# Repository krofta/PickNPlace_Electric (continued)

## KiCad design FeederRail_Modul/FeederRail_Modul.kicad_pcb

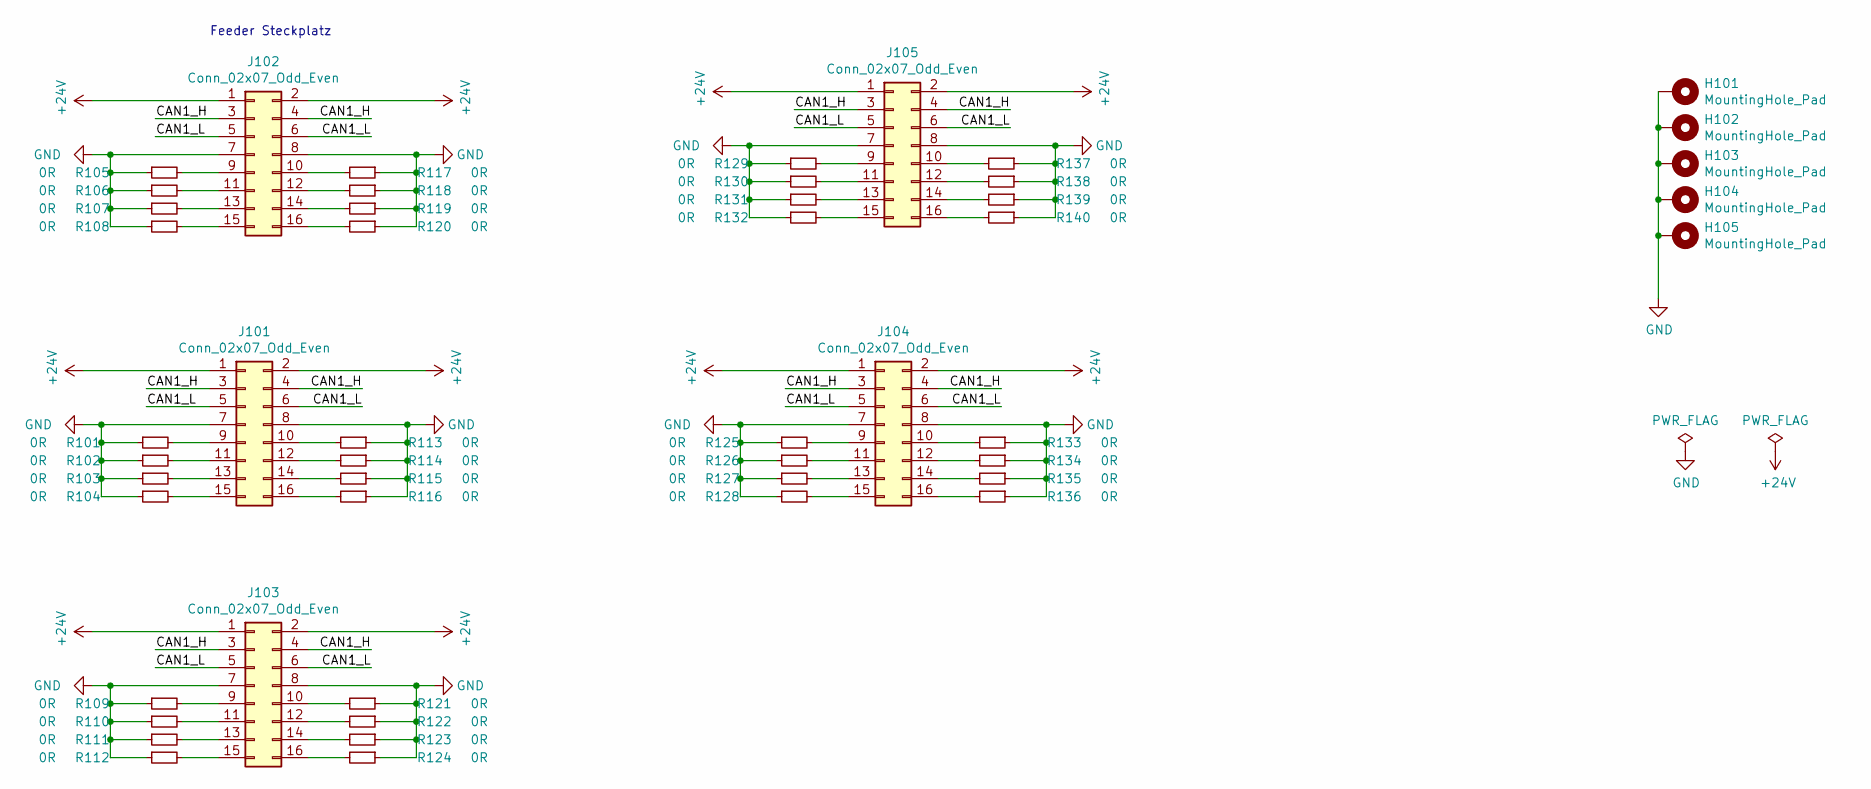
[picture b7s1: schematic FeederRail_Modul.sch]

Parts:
H101, H102, H103, H104, H105: MountingHole_Pad; MountingHole_4mm_Pad_Via; LCSC 0
J101, J102, J103, J104, J105: Conn_02x07_Odd_Even; PinHeader_2x08_P2.54mm_Vertical; LCSC C30734
R101, R102, R103, R104, R105, R106, R107, R108, R109, R110, R111, R112, R113, R114, R115, R116, R117, R118, R119, R120, R121, R122, R123, R124, R125, R126, R127, R128, R129, R130, R131, R132, R133, R134, R135, R136, R137, R138, R139, R140: 0R; R_0603_1608Metric; LCSC C384298

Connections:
+24V: J101.1, J101.2, J102.1, J102.2, J103.1, J103.2, J104.1, J104.2, J105.1, J105.2
/CAN1_H: J101.3, J101.4, J102.3, J102.4, J103.3, J103.4, J104.3, J104.4, J105.3, J105.4
/CAN1_L: J101.5, J101.6, J102.5, J102.6, J103.5, J103.6, J104.5, J104.6, J105.5, J105.6
GND: H101.1, H102.1, H103.1, H104.1, H105.1, J101.7, J101.8, J102.7, J102.8, J103.7, J103.8, J104.7, J104.8, J105.7, J105.8, R101.1, R102.1, R103.1, R104.1, R105.1, R106.1, R107.1, R108.1, R109.1, R110.1, R111.1, R112.1, R113.1, R114.1, R115.1, R116.1, R117.1, R118.1, R119.1, R120.1, R121.1, R122.1, R123.1, R124.1, R125.1, R126.1, R127.1, R128.1, R129.1, R130.1, R131.1, R132.1, R133.1, R134.1, R135.1, R136.1, R137.1, R138.1, R139.1, R140.1
unnamed: J101.9, R101.2
unnamed: J101.10, R113.2
unnamed: J101.11, R102.2
unnamed: J101.12, R114.2
unnamed: J101.13, R103.2
unnamed: J101.14, R115.2
unnamed: J101.15, R104.2
unnamed: J101.16, R116.2
unnamed: J102.9, R105.2
unnamed: J102.10, R117.2
unnamed: J102.11, R106.2
unnamed: J102.12, R118.2
unnamed: J102.13, R107.2
unnamed: J102.14, R119.2
unnamed: J102.15, R108.2
unnamed: J102.16, R120.2
unnamed: J103.9, R109.2
unnamed: J103.10, R121.2
unnamed: J103.11, R110.2
unnamed: J103.12, R122.2
unnamed: J103.13, R111.2
unnamed: J103.14, R123.2
unnamed: J103.15, R112.2
unnamed: J103.16, R124.2
unnamed: J104.9, R125.2
unnamed: J104.10, R133.2
unnamed: J104.11, R126.2
unnamed: J104.12, R134.2
unnamed: J104.13, R127.2
unnamed: J104.14, R135.2
unnamed: J104.15, R128.2
unnamed: J104.16, R136.2
unnamed: J105.9, R129.2
unnamed: J105.10, R137.2
unnamed: J105.11, R130.2
unnamed: J105.12, R138.2
unnamed: J105.13, R131.2
unnamed: J105.14, R139.2
unnamed: J105.15, R132.2
unnamed: J105.16, R140.2

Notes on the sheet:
Feeder Steckplatz

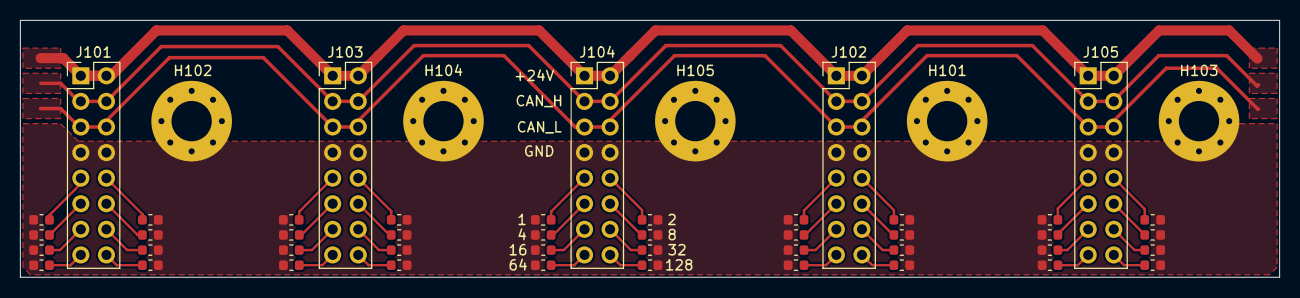
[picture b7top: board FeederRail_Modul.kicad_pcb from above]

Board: 2 copper layers, 125.0 x 25.5 mm, 50 parts (0 on the bottom side), 44 nets.

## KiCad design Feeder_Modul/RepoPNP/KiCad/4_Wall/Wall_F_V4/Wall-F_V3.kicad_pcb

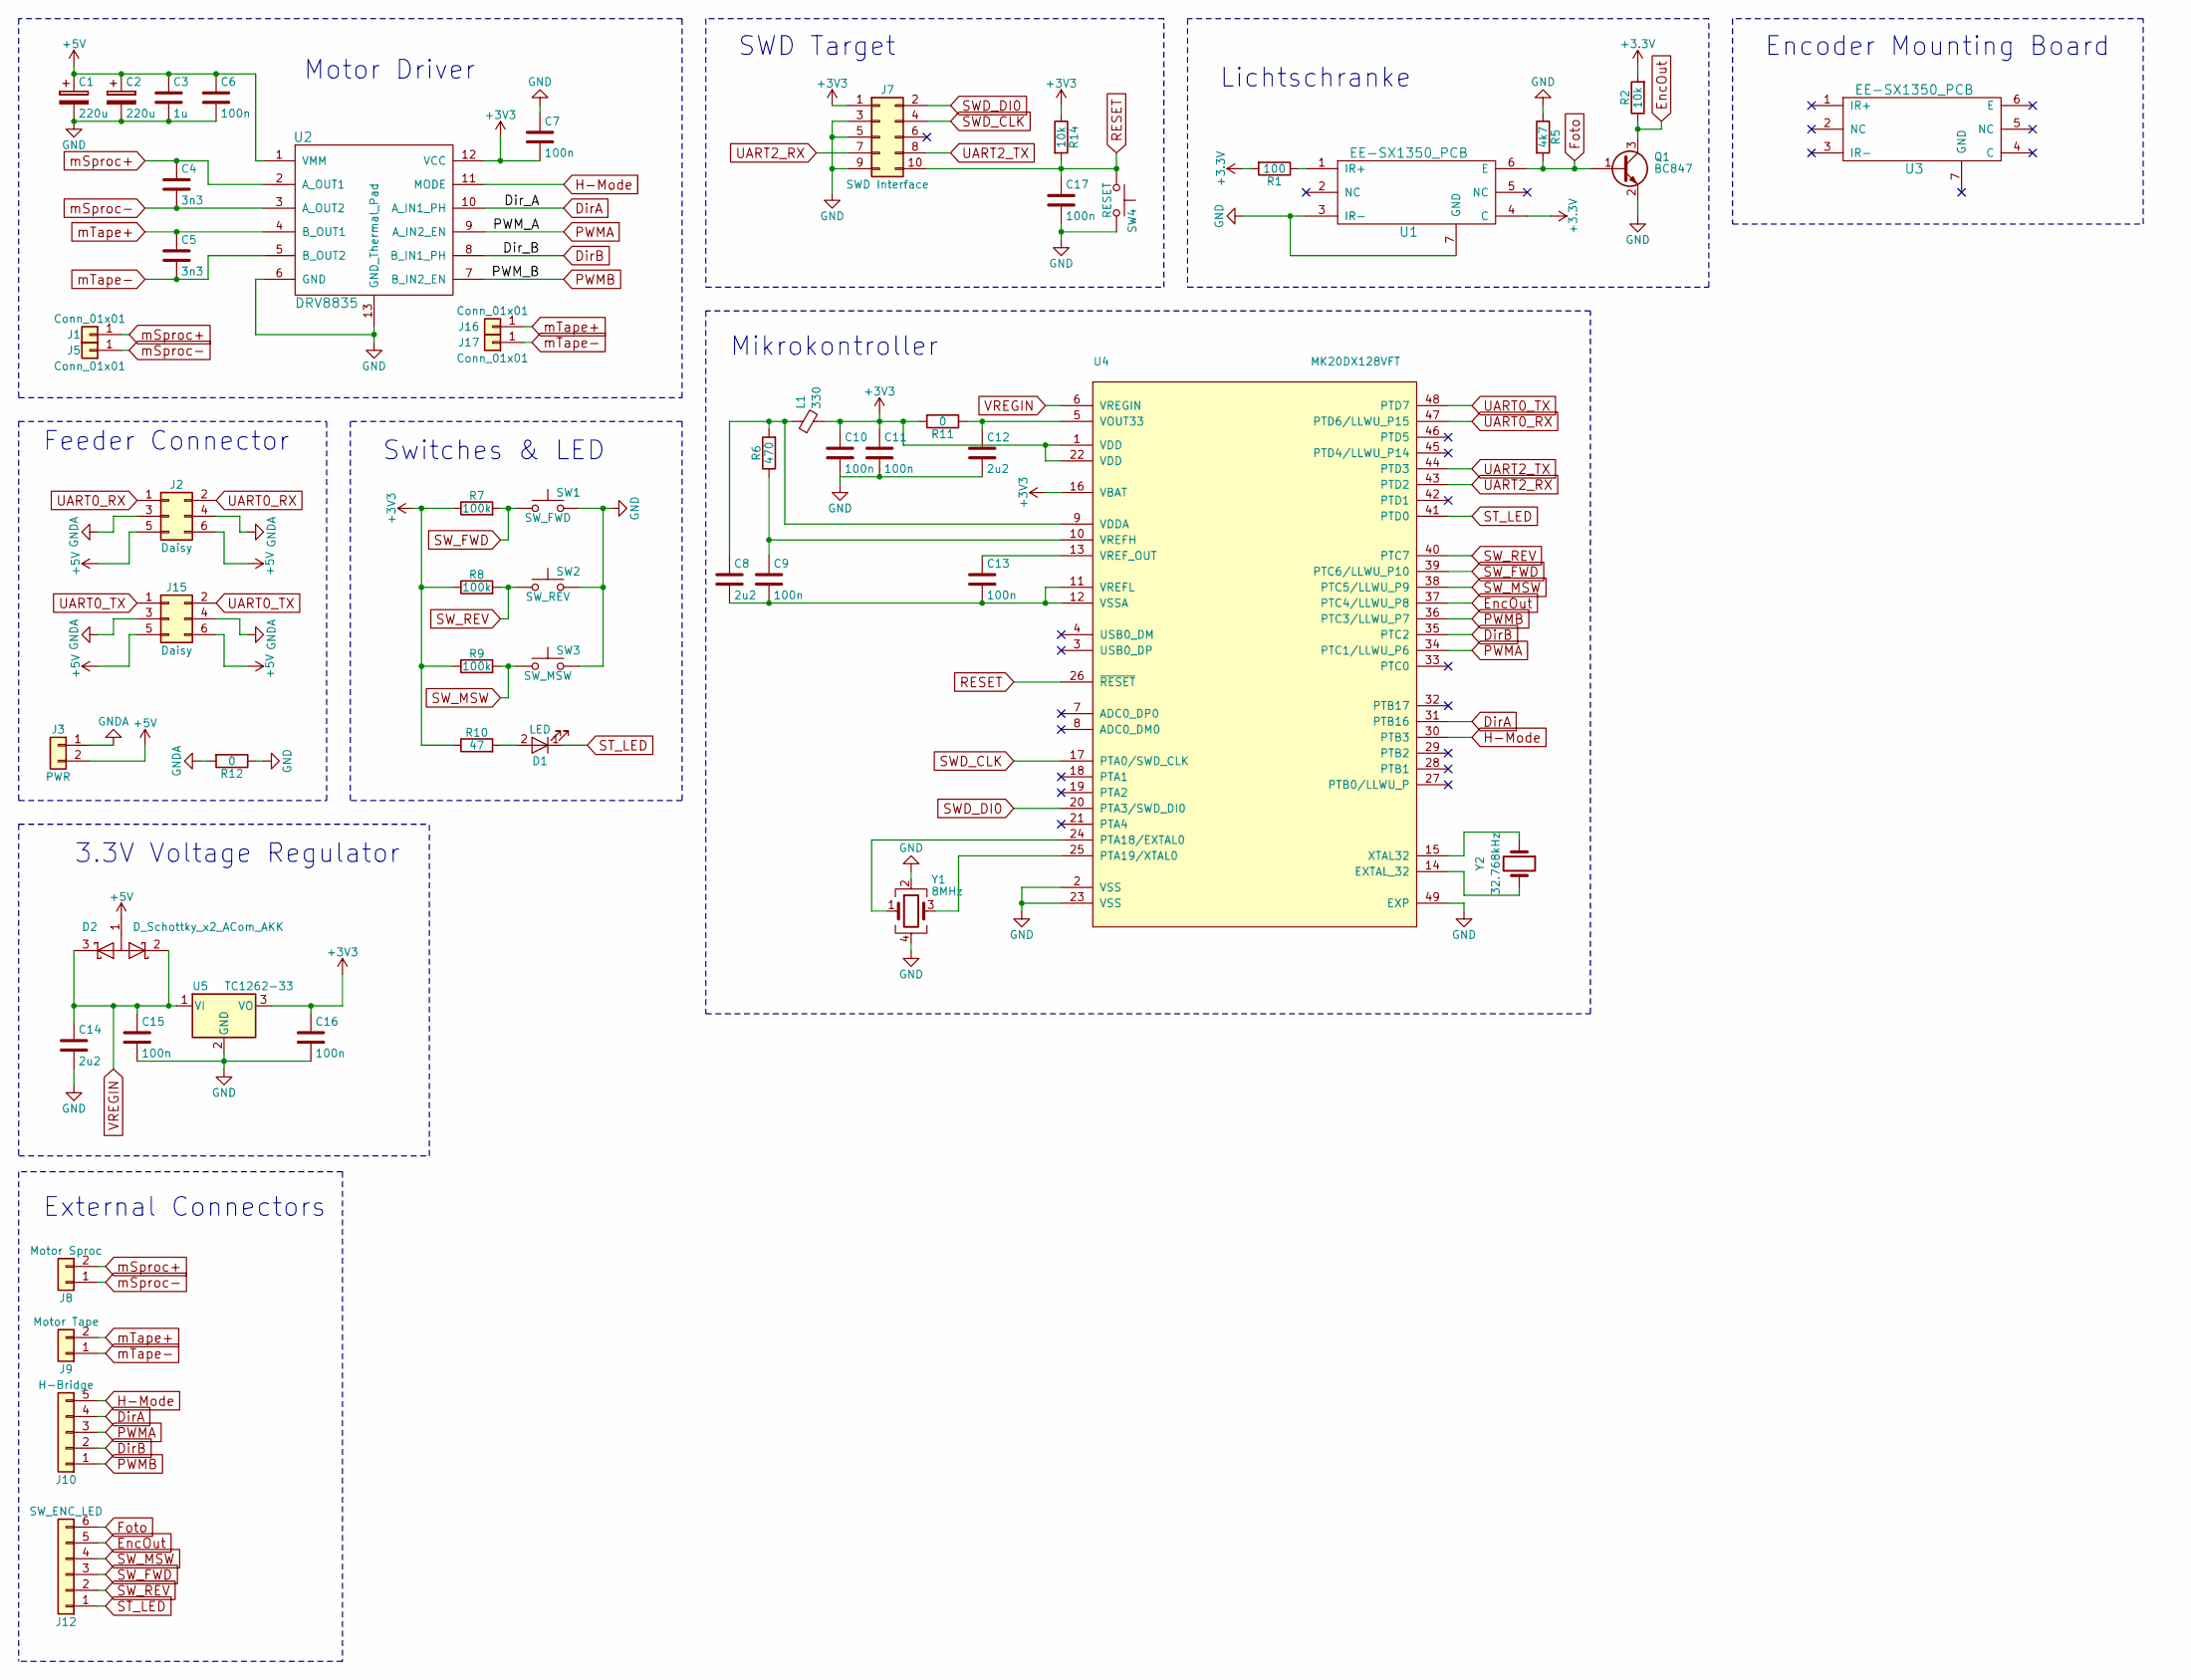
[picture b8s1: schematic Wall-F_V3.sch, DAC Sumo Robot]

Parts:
C1, C2: 220u; CP_Elec_6.3x7.7
C3: 1u; C_0805
C4, C5: 3n3; C_0805
C6, C7, C9, C10, C11, C13, C15, C16, C17: 100n; C_0805
C8, C12, C14: 2u2; C_0805
D1: LED; LED_0805
D2: D_Schottky_x2_ACom_AKK; SOT-23
J1, J5, J16, J17: Conn_01x01; Pin_Header_Straight_1x01_Pitch2.54mm
J2, J15: Daisy; Pin_Header_Angled_2x03_Pitch2.54mm
J3: PWR; Pin_Header_Straight_1x02_Pitch2.54mm
J7: SWD Interface; Pin_Header_Straight_2x05_Pitch1.27mm_SMD
J8: Motor Sproc; Pin_Header_Straight_1x02_Pitch2.54mm
J9: Motor Tape; Pin_Header_Straight_1x02_Pitch2.54mm
J10: H-Bridge; Pin_Header_Straight_1x05_Pitch2.54mm
J12: SW_ENC_LED; Pin_Header_Straight_1x06_Pitch2.54mm
L1: 330; L_0805
Q1: BC847; SOT-23
R1: 100; R_0805
R2, R14: 10k; R_0805
R5: 4k7; R_0805
R6: 470; R_0805
R7, R8, R9: 100k; R_0805
R10: 47; R_0805
R11, R12: 0; R_0805
SW1: SW_FWD; SW_SPST_B3S-1000_LONG
SW2: SW_REV; SW_SPST_B3S-1000_LONG
SW3: SW_MSW; Pin_Header_Straight_1x02_Pitch2.54mm
SW4: RESET; SW_SPST_B3S-1000_LONG
U1: EE-SX1350_PCB; EESX1350_PCB_V4
U2: DRV8835; WSON-12-1EP_3x2mm_Pitch0.5mm
U3: EE-SX1350_PCB; EESX1350_Board
U4: MK20DX128VFT; QFN-48-1EP_7x7mm_Pitch0.5mm
U5: TC1262-33; SOT-223-3_TabPin2
Y1: 8MHz; Crystal_SMD_0603-4pin_6.0x3.5mm
Y2: 32.768kHz; R_0805

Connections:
+5V: C1.1, C2.1, C3.1, C6.1, D2.1 (A), J2.5, J2.6, J3.2, J15.5, J15.6, U2.1 (VMM)
DirA: J10.4, U2.10 (A_IN1_PH), U4.31 (PTB16)
DirB: J10.2, U2.8 (B_IN1_PH), U4.35 (PTC2)
EncOut: J12.5, Q1.3 (C), R2.1, U4.37 (PTC4/LLWU_P8)
Foto: J12.6, Q1.1 (B), R5.2, U1.6 (E)
GND: C1.2, C2.2, C3.2, C6.2, C7.1, C10.2, C11.2, C12.2, C14.2, C15.2, C16.2, C17.2, J7.3, J7.5, J7.9, Q1.2 (E), R5.1, R12.1, SW1.2, SW2.2, SW3.2, SW4.2, U1.2 (NC), U1.3 (IR-), U1.7 (GND), U2.6 (GND), U2.13 (GND_Thermal_Pad), U4.2 (VSS), U4.23 (VSS), U4.49 (EXP), U5.2 (GND), Y1.2, Y1.4
GNDA: J2.3, J2.4, J3.1, J15.3, J15.4, R12.2
H-Mode: J10.5, U2.11 (MODE), U4.30 (PTB3)
unnamed: C8.1, L1.1, R6.2, U4.9 (VDDA)
unnamed: C9.1, R6.1, U4.10 (VREFH)
unnamed: C12.1, R11.1, U4.5 (VOUT33)
unnamed: C13.1, U4.13 (VREF_OUT)
unnamed: C8.2, C9.2, C13.2, U4.11 (VREFL), U4.12 (VSSA)
unnamed: D1.2 (A), R10.2
unnamed: R1.1, U1.1 (IR+)
unnamed: U4.14 (EXTAL_32), Y2.2
unnamed: U4.15 (XTAL32), Y2.1
unnamed: U4.24 (PTA18/EXTAL0), Y1.1
unnamed: U4.25 (PTA19/XTAL0), Y1.3
PWMA: J10.3, U2.9 (A_IN2_EN), U4.34 (PTC1/LLWU_P6)
PWMB: J10.1, U2.7 (B_IN2_EN), U4.36 (PTC3/LLWU_P7)
RESET: C17.1, J7.10, R14.2, SW4.1, U4.26 (~RESET)
ST_LED: D1.1 (K), J12.1, U4.41 (PTD0)
SWD_CLK: J7.4, U4.17 (PTA0/SWD_CLK)
SWD_DI0: J7.2, U4.20 (PTA3/SWD_DI0)
SW_FWD: J12.3, R7.2, SW1.1, U4.39 (PTC6/LLWU_P10)
SW_MSW: J12.4, R9.2, SW3.1, U4.38 (PTC5/LLWU_P9)
SW_REV: J12.2, R8.2, SW2.1, U4.40 (PTC7)
UART1_RX: J7.7, U4.43 (PTD2)
UART1_TX: J7.8, U4.44 (PTD3)
UART2_RX: J2.1, J2.2, U4.47 (PTD6/LLWU_P15)
UART2_TX: J15.1, J15.2, U4.48 (PTD7)
VREGIN: C14.1, C15.1, D2.2 (K), D2.3 (K), U4.6 (VREGIN), U5.1 (VI)
mSproc+: C4.1, J1.1, J8.2, U2.2 (A_OUT1)
mSproc-: C4.2, J5.1, J8.1, U2.3 (A_OUT2)
mTape+: C5.1, J9.2, J16.1, U2.4 (B_OUT1)
mTape-: C5.2, J9.1, J17.1, U2.5 (B_OUT2)

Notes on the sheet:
Motor Driver
Lichtschranke
Feeder Connector
Switches & LED
External Connectors
3.3V Voltage Regulator
SWD Target
Encoder Mounting Board
Mikrokontroller

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
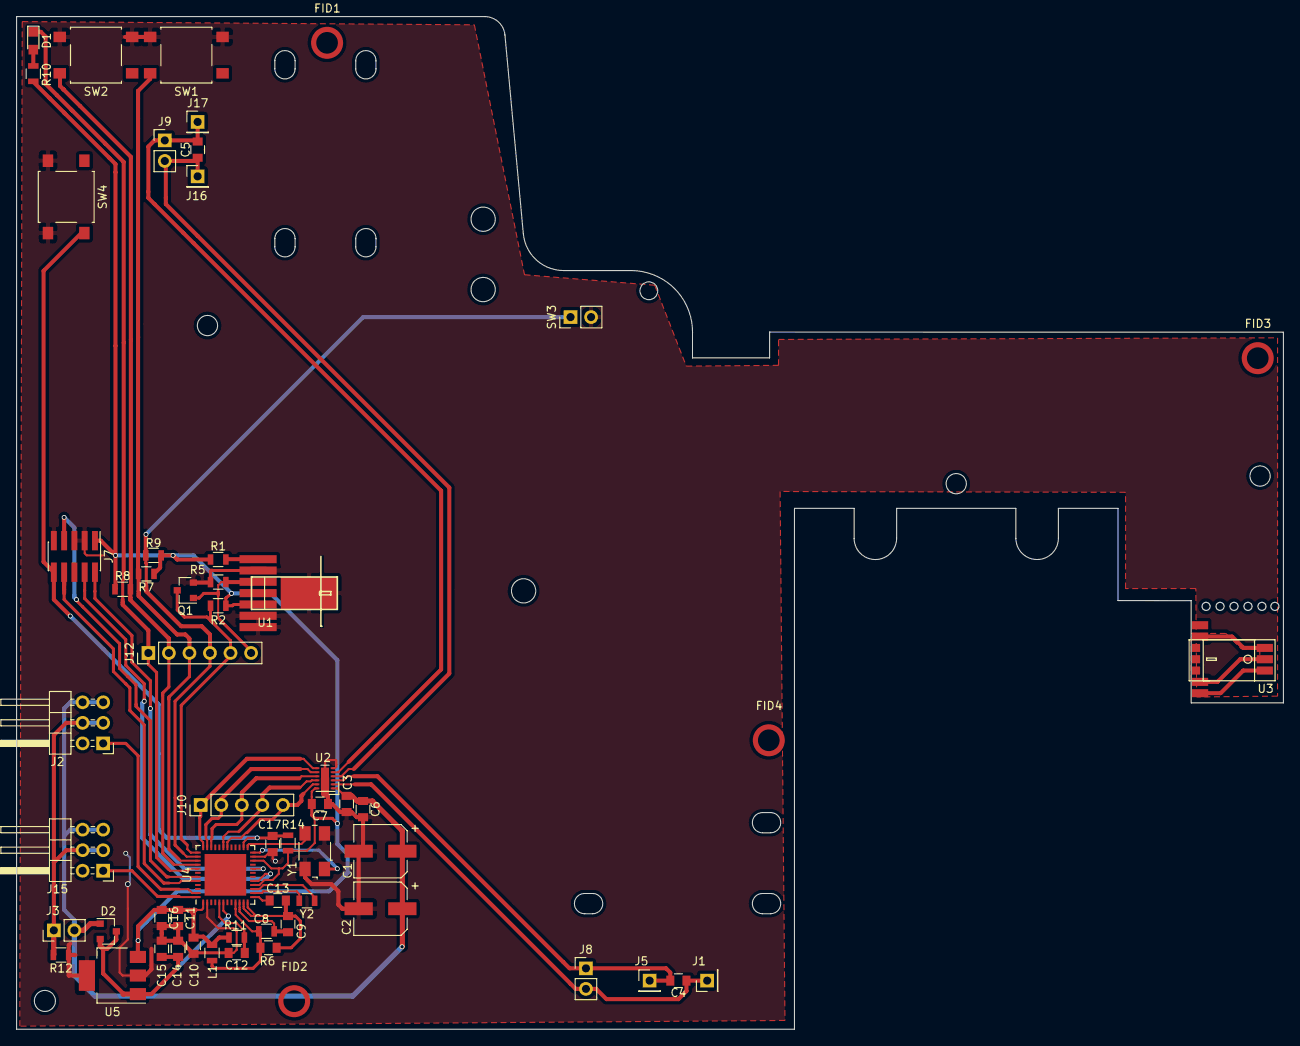
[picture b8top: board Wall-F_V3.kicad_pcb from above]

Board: 2 copper layers, 156.6 x 125.2 mm, 59 parts (0 on the bottom side), 38 nets.

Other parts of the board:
FID1, FID2, FID3: Fiducial_1mm_Dia_2mm_Outer; Fiducial_Modern_CopperTop
FID4: Fiducial_Modern_CopperTop

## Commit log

2020-12-06 Testsoftware for ImageProcessing in c programmiert
2020-12-21 CPU und RAM ausgesucht, CPU Board und StepperBoard sind modular
2021-01-11 SDRAM verdrahtet, STLINK conn, NRST, BOOT0, Oszillator. TODO: RS422, DCMI, SPI-Display, SD-Karte, Encoder, Step-Down
2021-01-12 rs485, sdcard, display connector, rotary encoder, camera connector; Step down and power
2021-01-15 sd card footprint, step down regler
2021-01-16 alle parts geplaced. kann gerouted werden. LEDs für Status hinzufügen: run, fault, 5v, 3v3
2021-01-17 ram verdrahtung nicht optimal - noch mal versuchen
2021-01-17 RAM auf die rückseite verlegt, alles auf 55mm length gematcht
2021-01-17 RAM (55mm) und SDCARD (65 mm) length gematcht, fehlt noch DCMI
2021-01-17 PCB fertig. Length matching RAM 55mm, DCMI 90mm, SD-Card 65mm.. Pins für interfaces erneut mit Evalboard und CubeMX muxtool verglichen
2021-01-17 STM32F401 für motoransteuerung gewählt. TODO: motoransteuerung und leistungsteil trennen, damit für schnelle fehlerbehebung modul getauscht werden kann
2021-01-18 RS485 durch CAN-Bus ausgetauscht, DIP-Switches für Adresse hinzugefügt
2021-01-18 motor controller von stepper-treibern getrennt, sodass es modular ist. Libraries werden nun übergreifend von allen projekten verwendet
2021-01-19 RepoPNP von Huber genauer unter die Lupe genommen
2021-01-19 SprocketWorm um 90 Grad gedreht und verlängert. TODO: Halterungslöcher machen und Halterung für lager erstellen
2021-01-19 LagerHalter für Wurmgetriebe hinzugefügt
2021-01-19 Fehlt nur noch das 5x11x5 lager
2021-01-20 neue PCB, LaderHalter, Wurmgetriebe mit Wellenverlängerung als STEP
2021-01-23 Verzeichnis aufgeräumt, README hinzugefügt
2021-01-23 stepper board fertig gestellt
2021-01-24 Conroller Modul Schaltplan fertig
2021-01-25 Controller Board geplaced
2021-01-26 DXF für outline
2021-01-26 Schaltplan für Feeder fast fertig, Wichtige Komponenten auf der PCB geplaced. DXF Outline und Annotations für Bauteile konnten erfolgreich importiert werden
2021-01-27 PCB fast fertig geroutet, I2C EEPROM hinzugefügt
2021-01-27 Feeder fertig
2021-01-27 Controller Modul und CV Modul Can schaltung berichtigt. CV Modul abgerundete Ecken r=5mm. TODO: IO Modul, Feeder-Steckplätze, Display Modul
2021-01-28 IO-Modul fertig
2021-01-28 Feeder Microswitch für Tape Motor hinzugefügt. Einige 3D Step Modelle hinzugefügt. Stepper Board die Ecken abgerundet.
2021-01-28 Neue Lichtschranke für Feeder rausgesucht. TODO: neuer Footprint, Aljosha -> Update der CAD Daten
2021-01-28 Pulldown am CAN-Phy auf 1K reduzieren für high speed mode
2021-01-29 Controller Modul geroutet
2021-02-01 display modul fertig
2021-02-02 Leere Symbole mit leeren Footprints hinzugefügt für BOM export
2021-02-02 BOM für LCSC überarbeitet. Tool für BOM export modifiziert
2021-02-02 Feeder Rails hinzugefügt
2021-02-03 Feeder Rail mit Step files geprüft. Connector am Feeder verschoeben. Halter für Lager muss angepasst werden.
2021-02-03 CV Modul Reset Button hinzugefügt
2021-02-03 CV Modul Strong 1K Pulldown CAN Phy für Fast Mode. STEP Modelle hinzugefügt. Connector für Kamera etwas nach rechts verschoben
2021-02-03 ESD Protection für Feeder Modul USB hinzugefügt, Status LED für Controller Modul hinzugefügt
2021-02-05 Fiducials auf allen Boards hinzugefügt
2021-03-12 ESD Protection überarbeitet, aber noch nicht fertig
2021-03-15 Änderungen für bestellung V01 - Bestellung abgeschickt
2021-03-31 Feeder Bugs behoben, Boards gebaut
2021-04-12 Kleine Bugs im Feeder behoben, Löcher für Lagerhalter hinzugefügt
